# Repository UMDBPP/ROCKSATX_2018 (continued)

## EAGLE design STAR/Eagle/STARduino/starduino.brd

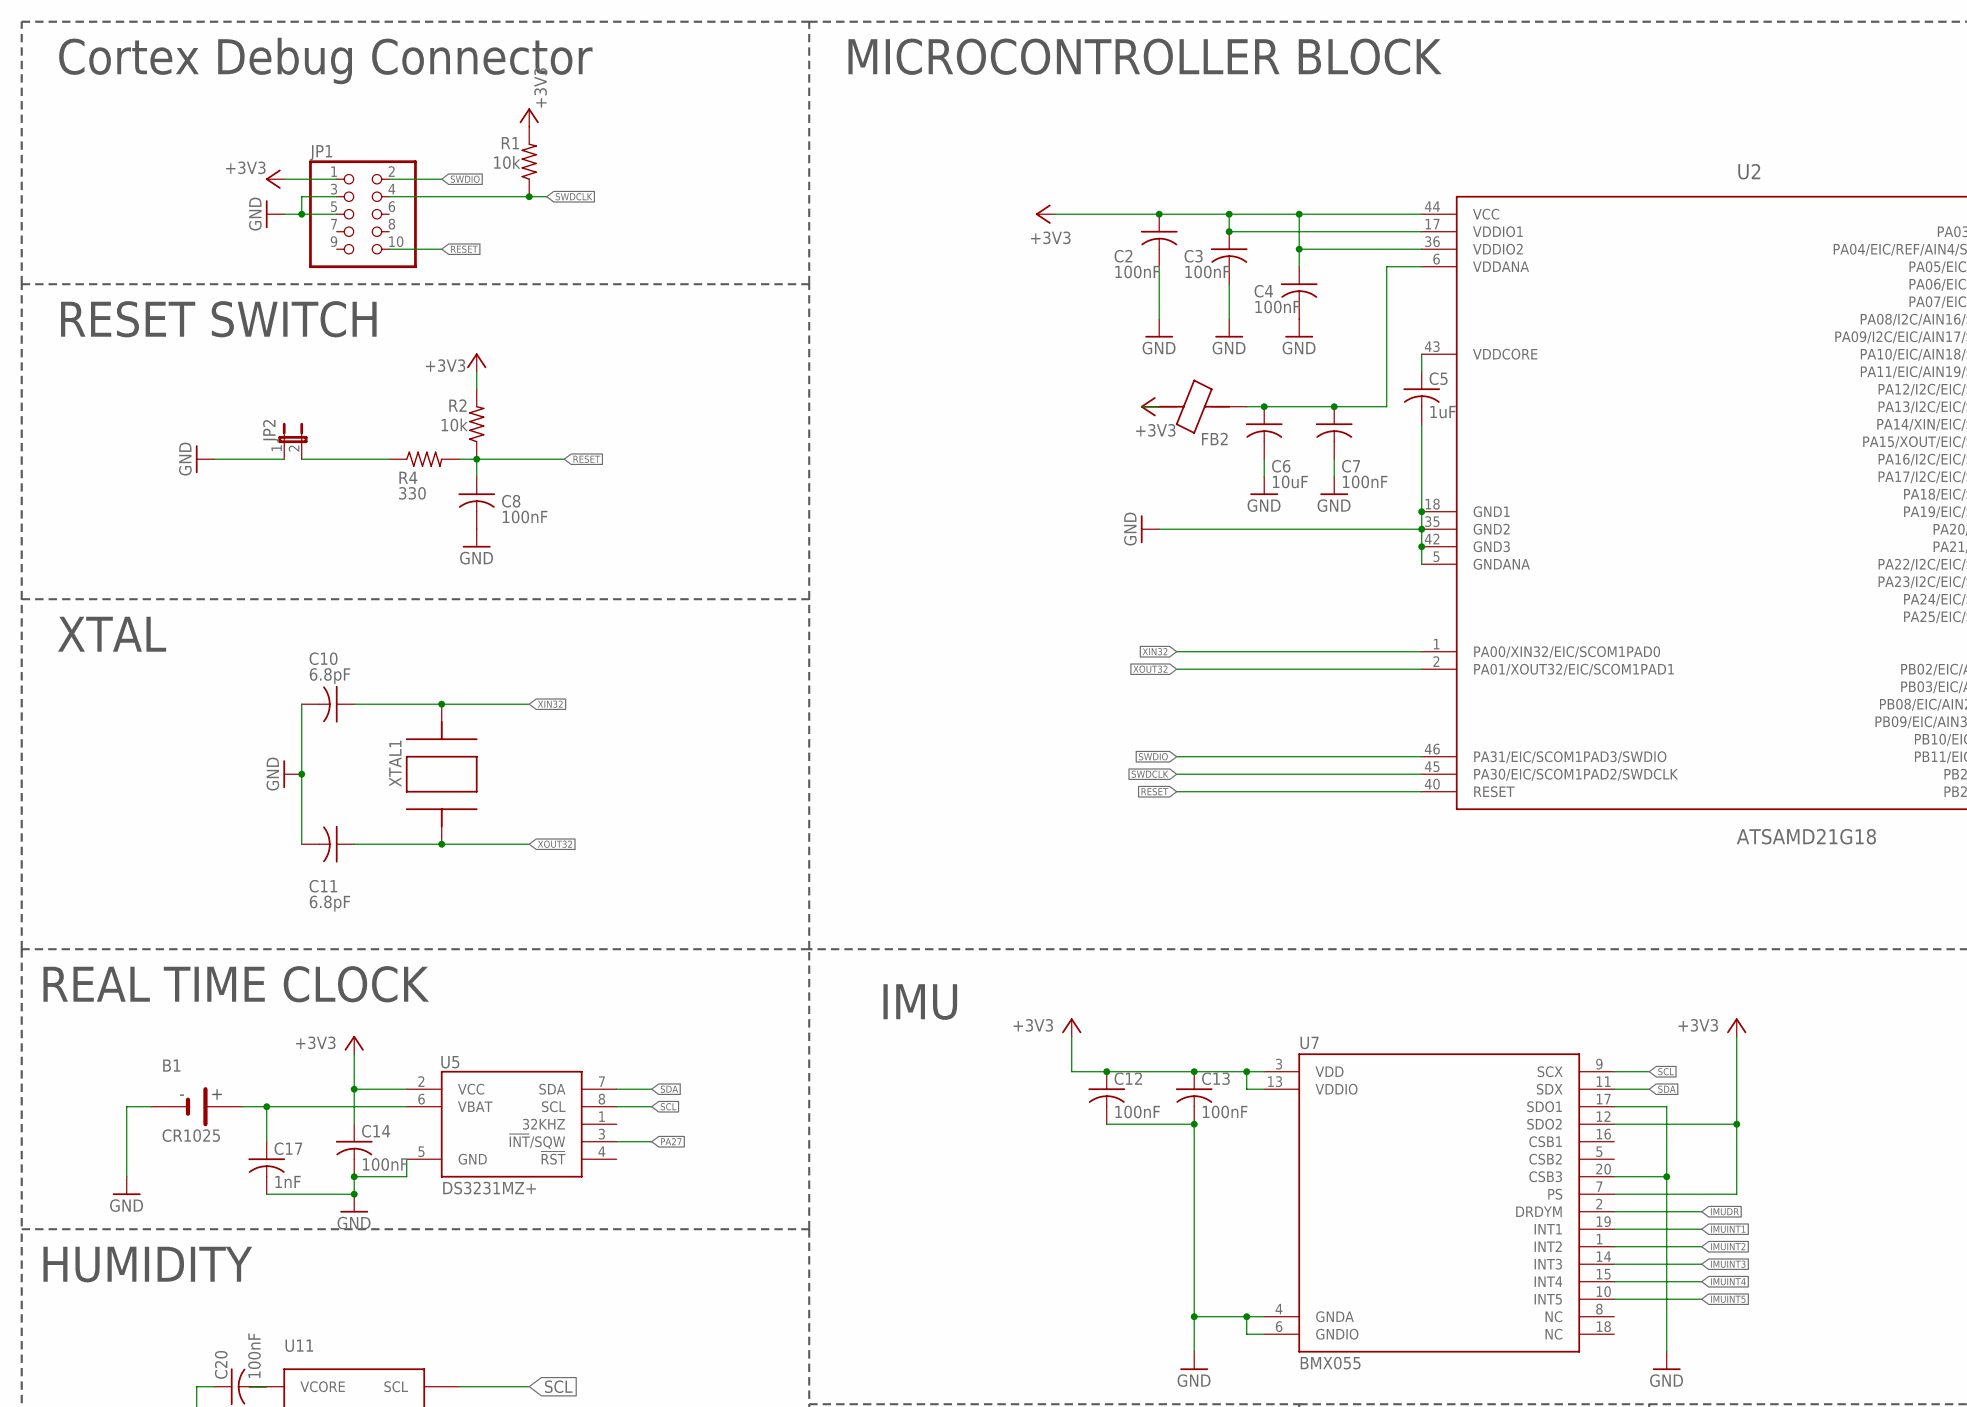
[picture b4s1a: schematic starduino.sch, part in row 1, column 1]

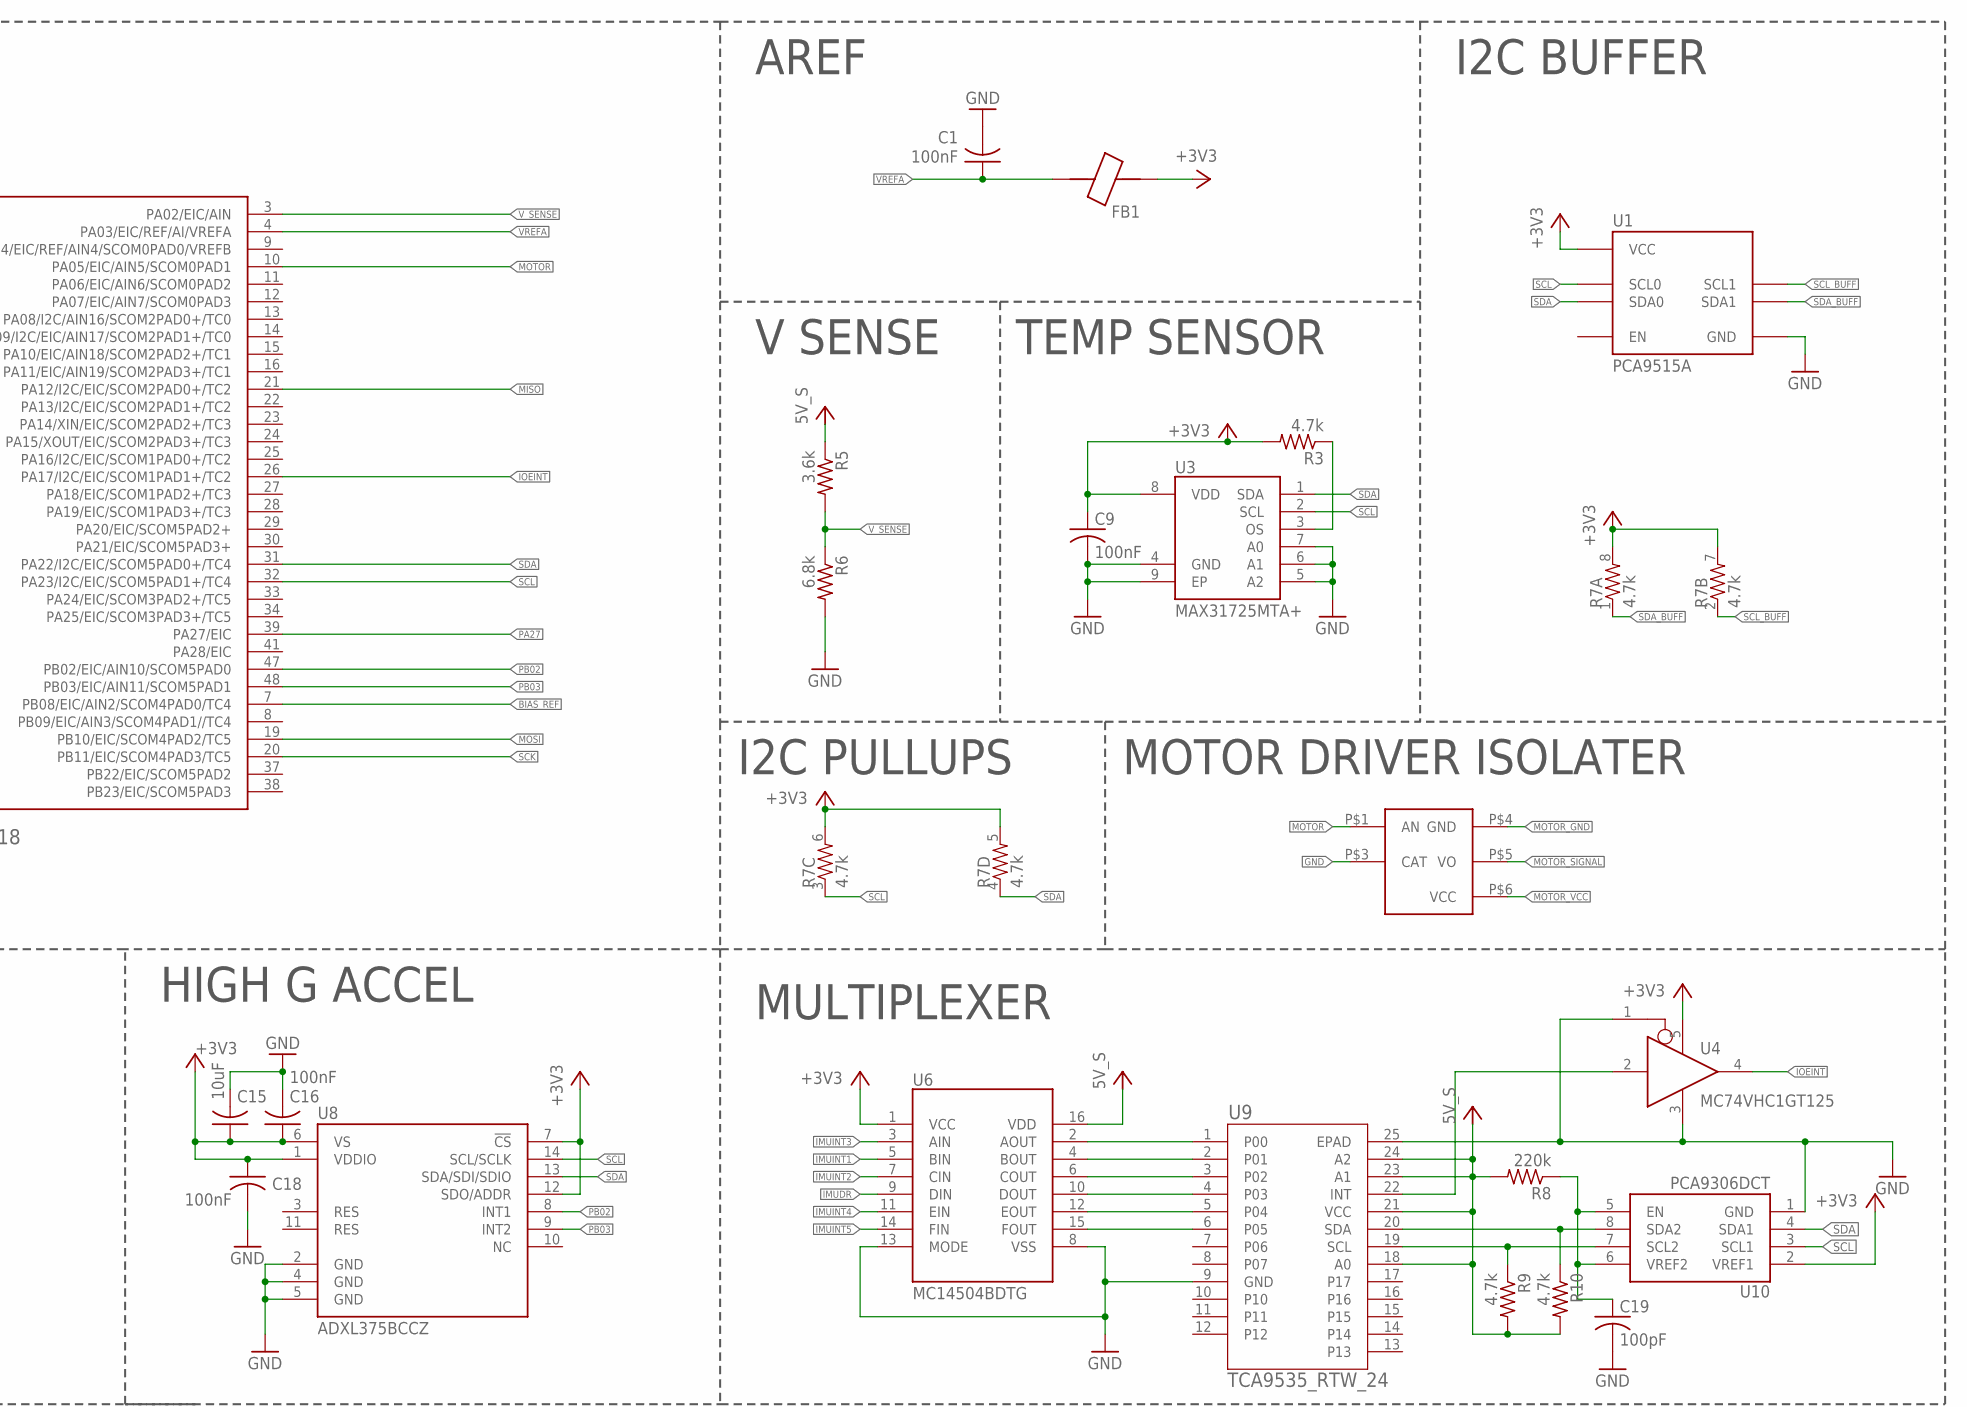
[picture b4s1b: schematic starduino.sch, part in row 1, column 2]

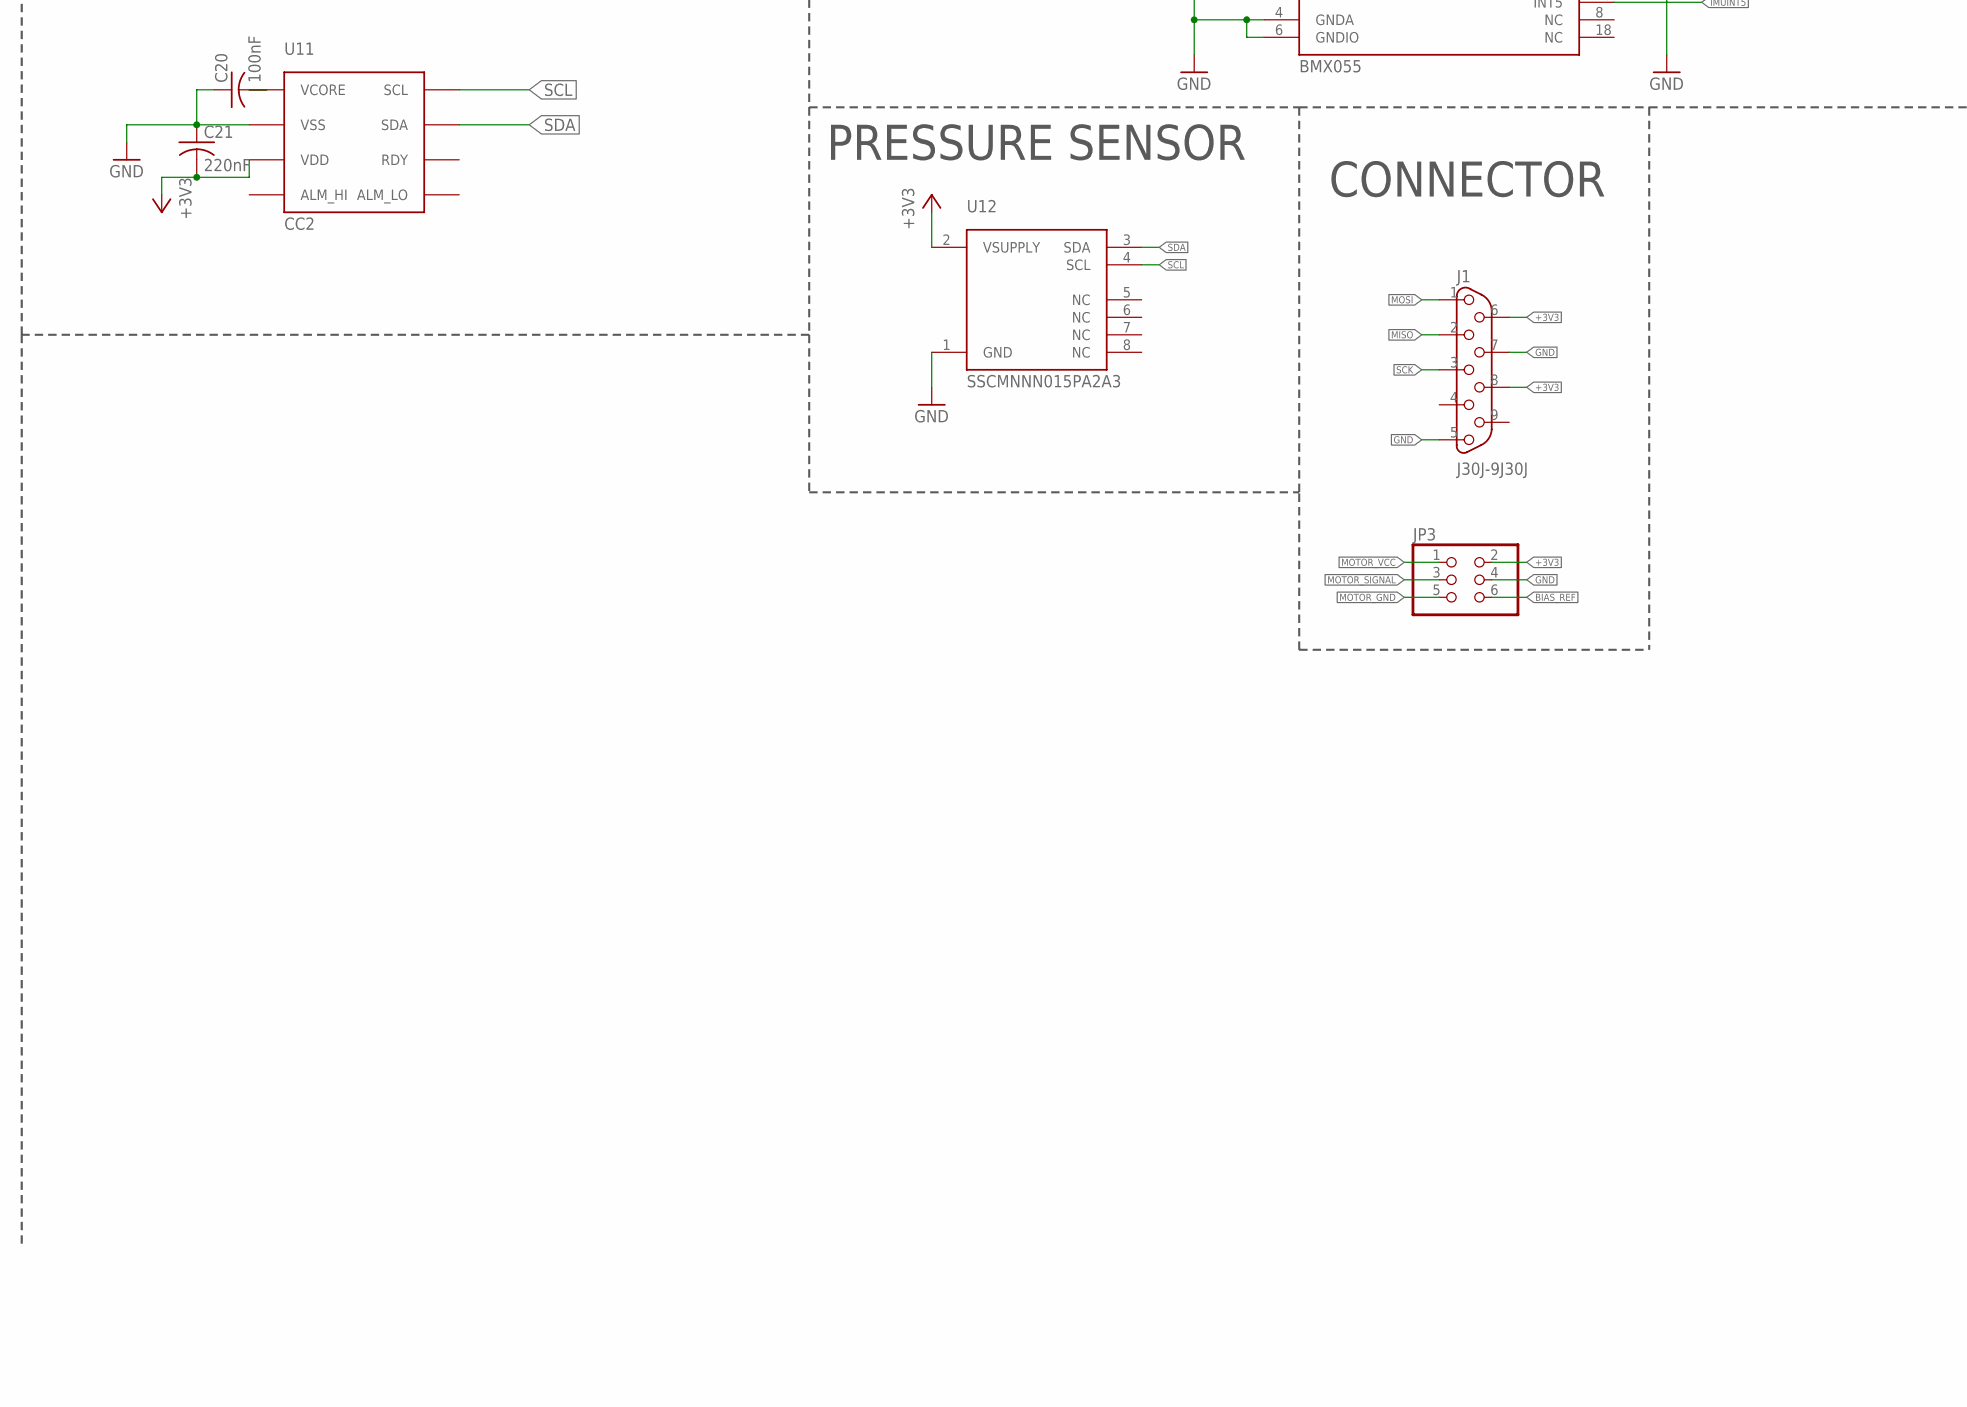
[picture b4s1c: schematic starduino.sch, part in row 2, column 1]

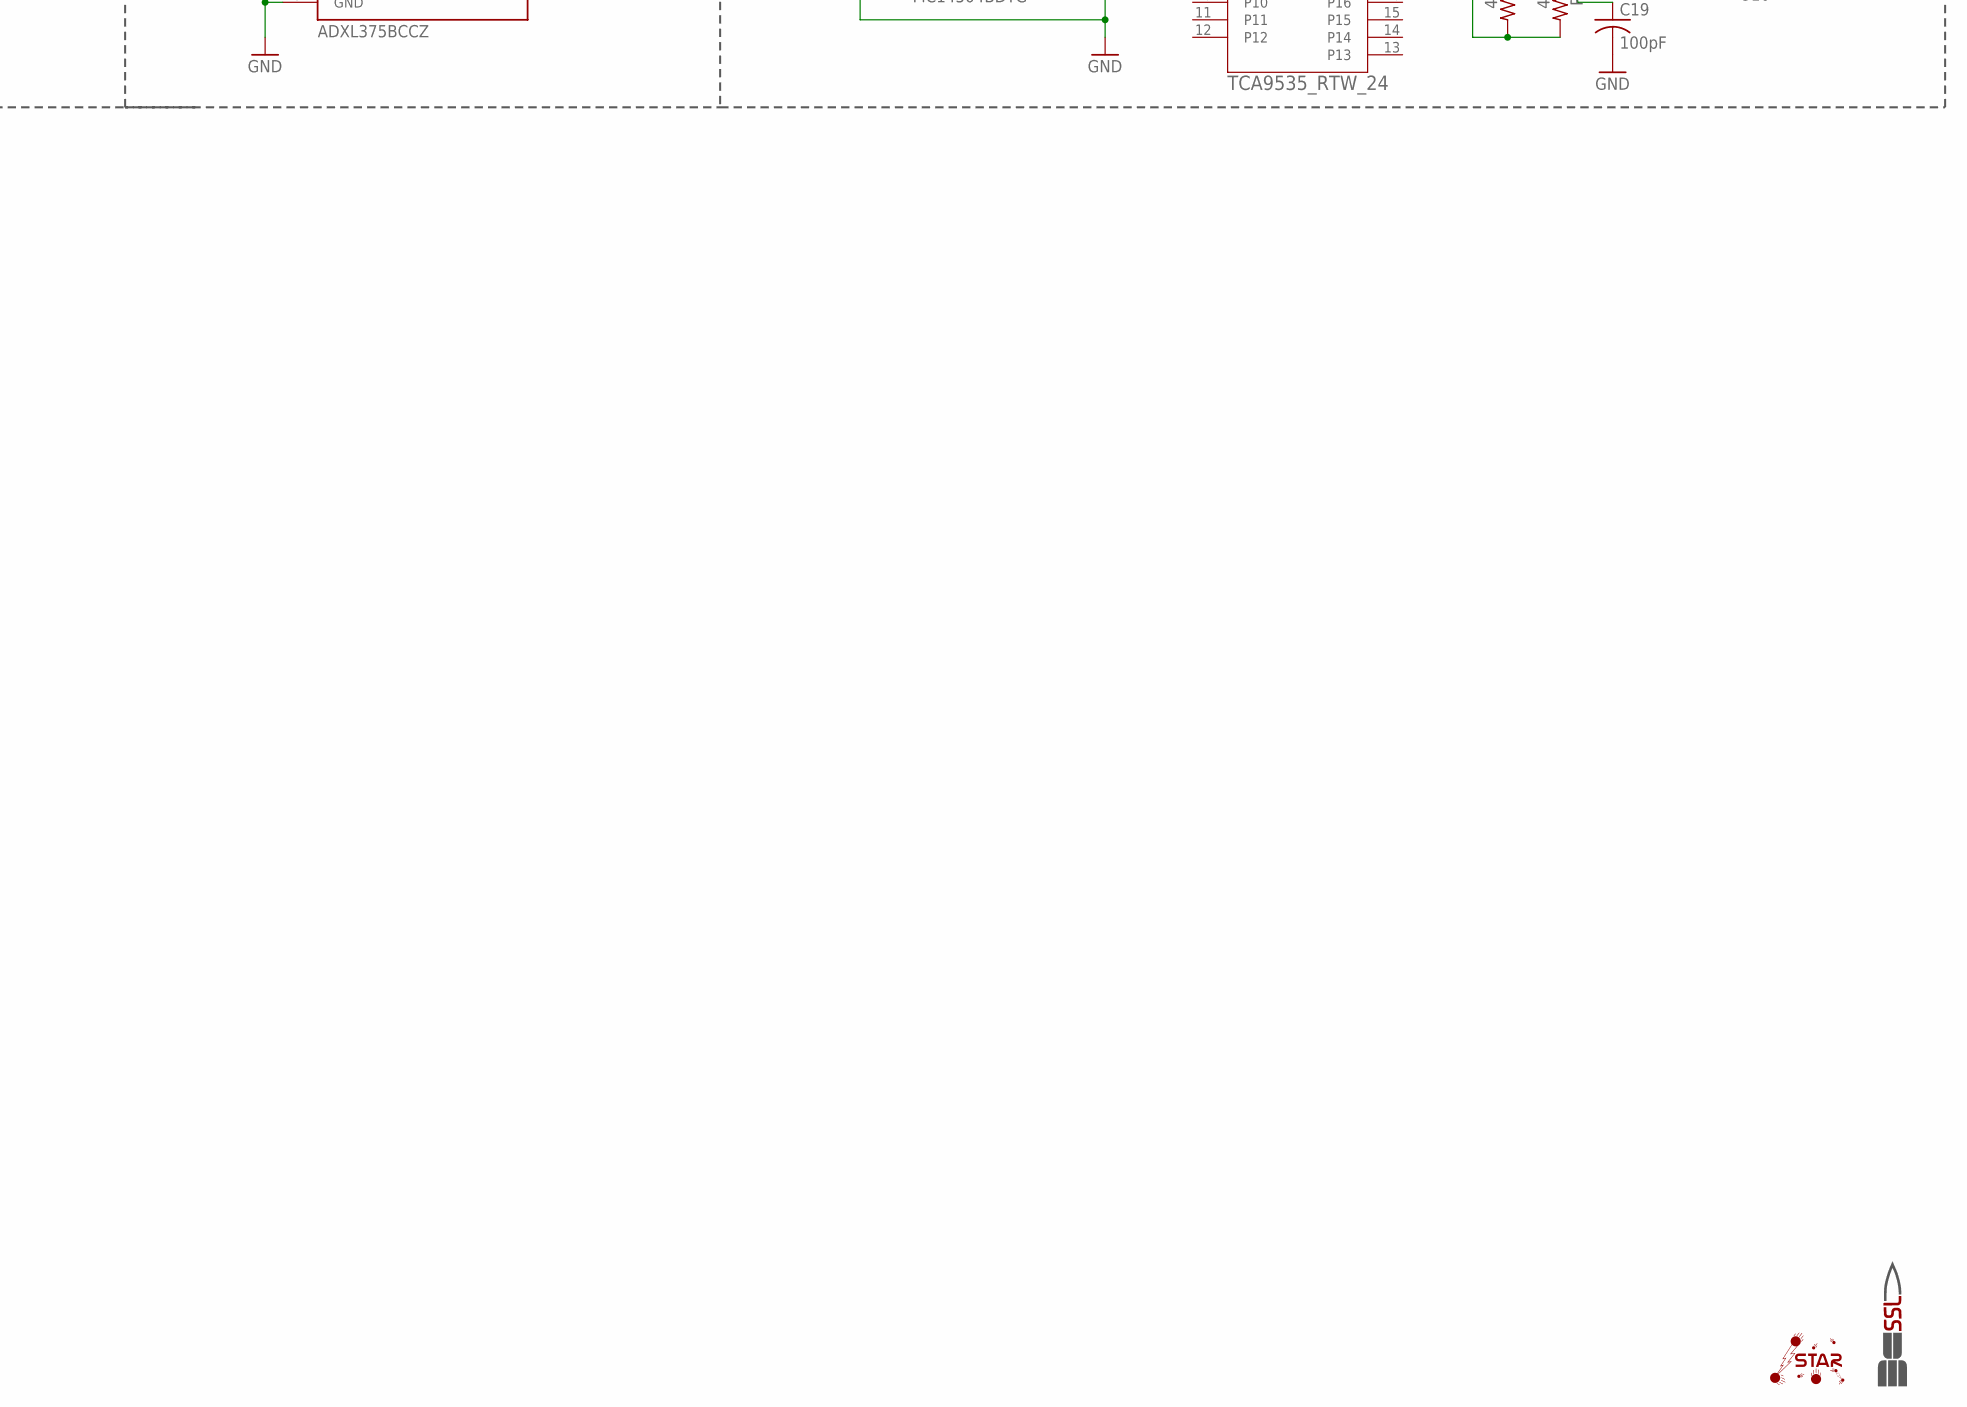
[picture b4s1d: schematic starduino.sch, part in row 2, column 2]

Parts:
B1: CR1025
C1, C2, C3, C4, C7, C8, C9, C12, C13, C14, C16, C18, C20: 100nF; C0603
C5: 1uF; C0603
C6, C15: 10uF; C0603
C10, C11: 6.8pF; C0603
C17: 1nF; C0603
C19: 100pF; C0603
C21: 220nF; C0603
FB1, FB2: BLM18KG221BH1D; 0603
IMAG1: SSL.3IN_SILK; SSL_SILK_.3IN
IMAG2: STAR; STAR_.3IN
J1: J30J-9J30J; ZKN-9
JP1: PINHD-2X5; 2X05
JP2: JUMPER-2PTH; 1X02
JP3: PINHD-2X3; 2X03
R1, R2: 10k; R0603
R3, R9, R10: 4.7k; R0603
R4: 330; R0603
R5: 3.6k; R0603
R6: 6.8k; R0603
R7: 4.7k; 0603-ARV
R8: 220k; R0603
U1: PCA9515A; TSSOP8
U2: ATSAMD21G18; 48-TQFP
U3: MAX31725MTA+; DFN-8
U4: MC74VHC1GT125; SC-70-5
U5: DS3231MZ+; SOIC-8
U6: MC14504BDTG; TSSOP16
U7: BMX055; LGA-20
U8: ADXL375BCCZ; LGA-14
U9: TCA9535_RTW_24; RTW24_2P45X2P45
U10: PCA9306DCT; SSOP8
U11: CC2
U12: SSCMNNN015PA2A3; HSC-SMT-8
U$1: FODM8061-D; SO5
XTAL1: ABS07AIG-32.768KHZ-1-T; 2-SMD

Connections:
5V_S: R5.1, R8.2, R9.2, R10.2, U6.16 (VDD), U9.18 (A0), U9.21 (VCC), U9.23 (A1), U9.24 (A2)
+3V3: C2.1, C3.1, C4.1, C9.1, C12.1, C13.1, C14.1, C15.1, C16.1, C18.1, C21.2, FB1.2, FB2.1, J1.6, J1.8, JP1.1, JP3.2, R1.2, R2.2, R3.2, R7.5 (2), R7.6 (2), R7.7 (2), R7.8 (2), U1.P$8 (VCC), U2.17 (VDDIO1), U2.36 (VDDIO2), U2.44 (VCC), U3.8 (VDD), U4.5 (VIN), U5.2 (VCC), U6.1 (VCC), U7.3 (VDD), U7.7 (PS), U7.12 (SDO2), U7.13 (VDDIO), U8.1 (VDDIO), U8.6 (VS), U8.7 (!CS!), U8.12 (SDO/ADDR), U10.2 (VREF1), U11.P$7 (VDD), U12.2 (VSUPPLY)
BIAS_REF: JP3.6, U2.7 (PB08/EIC/AIN2/SCOM4PAD0/TC4)
GND: B1.3 (-), C1.2, C2.2, C3.2, C4.2, C5.2, C6.2, C7.2, C8.2, C9.2, C10.2, C11.2, C12.2, C13.2, C14.2, C15.2, C16.2, C17.2, C18.2, C19.2, C20.1, C21.1, J1.5, J1.7, JP1.3, JP1.5, JP2.1, JP3.4, R6.2, U1.P$4 (GND), U2.5 (GNDANA), U2.18 (GND1), U2.35 (GND2), U2.42 (GND3), U3.4 (GND), U3.5 (A2), U3.6 (A1), U3.7 (A0), U3.9 (EP), U4.1 (OE), U4.3 (GND), U5.5 (GND), U6.8 (VSS), U6.13 (MODE), U7.4 (GNDA), U7.6 (GNDIO), U7.17 (SDO1), U7.20 (CSB3), U8.2 (GND), U8.4 (GND), U8.5 (GND), U9.9 (GND), U9.25 (EPAD), U10.1 (GND), U11.P$6 (VSS), U12.1 (GND), U$1.P$3 (CAT)
IMUDR: U6.9 (DIN), U7.2 (DRDYM)
IMUINT1: U6.5 (BIN), U7.19 (INT1)
IMUINT2: U6.7 (CIN), U7.1 (INT2)
IMUINT3: U6.3 (AIN), U7.14 (INT3)
IMUINT4: U6.11 (EIN), U7.15 (INT4)
IMUINT5: U6.14 (FIN), U7.10 (INT5)
IOEINT: U2.26 (PA17/I2C/EIC/SCOM1PAD1+/TC2), U4.4 (Y)
MISO: J1.2, U2.21 (PA12/I2C/EIC/SCOM2PAD0+/TC2)
MOSI: J1.1, U2.19 (PB10/EIC/SCOM4PAD2/TC5)
MOTOR: U2.10 (PA05/EIC/AIN5/SCOM0PAD1), U$1.P$1 (AN)
MOTOR_GND: JP3.5, U$1.P$4 (GND)
MOTOR_SIGNAL: JP3.3, U$1.P$5 (VO)
MOTOR_VCC: JP3.1, U$1.P$6 (VCC)
unnamed: C20.2, U11.P$5 (VCORE)
unnamed: C5.1, U2.43 (VDDCORE)
unnamed: R3.1, U3.3 (OS)
unnamed: JP2.2, R4.1
unnamed: B1.1 (+), B1.2 (+), C17.1, U5.6 (VBAT)
unnamed: C6.1, C7.1, FB2.2, U2.6 (VDDANA)
unnamed: U6.2 (AOUT), U9.1 (P00)
unnamed: U6.4 (BOUT), U9.2 (P01)
unnamed: U4.2 (A), U9.22 (INT)
unnamed: U6.6 (COUT), U9.3 (P02)
unnamed: U6.10 (DOUT), U9.4 (P03)
unnamed: U6.12 (EOUT), U9.5 (P04)
unnamed: U6.15 (FOUT), U9.6 (P05)
unnamed: R10.1, U9.20 (SDA), U10.8 (SDA2)
unnamed: R9.1, U9.19 (SCL), U10.7 (SCL2)
unnamed: C19.1, R8.1, U10.5 (EN), U10.6 (VREF2)
PA27: U2.39 (PA27/EIC), U5.3 (!INT!/SQW)
PB02: U2.47 (PB02/EIC/AIN10/SCOM5PAD0), U8.8 (INT1)
PB03: U2.48 (PB03/EIC/AIN11/SCOM5PAD1), U8.9 (INT2)
RESET: C8.1, JP1.10, R2.1, R4.2, U2.40 (RESET)
SCK: J1.3, U2.20 (PB11/EIC/SCOM4PAD3/TC5)
SCL: R7.3 (1), U1.P$2 (SCL0), U2.32 (PA23/I2C/EIC/SCOM5PAD1+/TC4), U3.2 (SCL), U5.8 (SCL), U7.9 (SCX), U8.14 (SCL/SCLK), U10.3 (SCL1), U11.P$4 (SCL), U12.4 (SCL)
SCL_BUFF: R7.2 (1), U1.P$7 (SCL1)
SDA: R7.4 (1), U1.P$3 (SDA0), U2.31 (PA22/I2C/EIC/SCOM5PAD0+/TC4), U3.1 (SDA), U5.7 (SDA), U7.11 (SDX), U8.13 (SDA/SDI/SDIO), U10.4 (SDA1), U11.P$3 (SDA), U12.3 (SDA)
SDA_BUFF: R7.1, U1.P$6 (SDA1)
SWDCLK: JP1.4, R1.1, U2.45 (PA30/EIC/SCOM1PAD2/SWDCLK)
SWDIO: JP1.2, U2.46 (PA31/EIC/SCOM1PAD3/SWDIO)
VREFA: C1.1, FB1.1, U2.4 (PA03/EIC/REF/AI/VREFA)
V_SENSE: R5.2, R6.1, U2.3 (PA02/EIC/AIN)
XIN32: C10.1, U2.1 (PA00/XIN32/EIC/SCOM1PAD0), XTAL1.P2 (2)
XOUT32: C11.1, U2.2 (PA01/XOUT32/EIC/SCOM1PAD1), XTAL1.P1 (1)

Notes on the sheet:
MICROCONTROLLER BLOCK
Cortex Debug Connector
RESET SWITCH
XTAL
AREF
V SENSE
I2C PULLUPS
HIGH G ACCEL
TEMP SENSOR
REAL TIME CLOCK
IMU
HUMIDITY
MULTIPLEXER
I2C BUFFER
PRESSURE SENSOR
CONNECTOR
MOTOR DRIVER ISOLATER

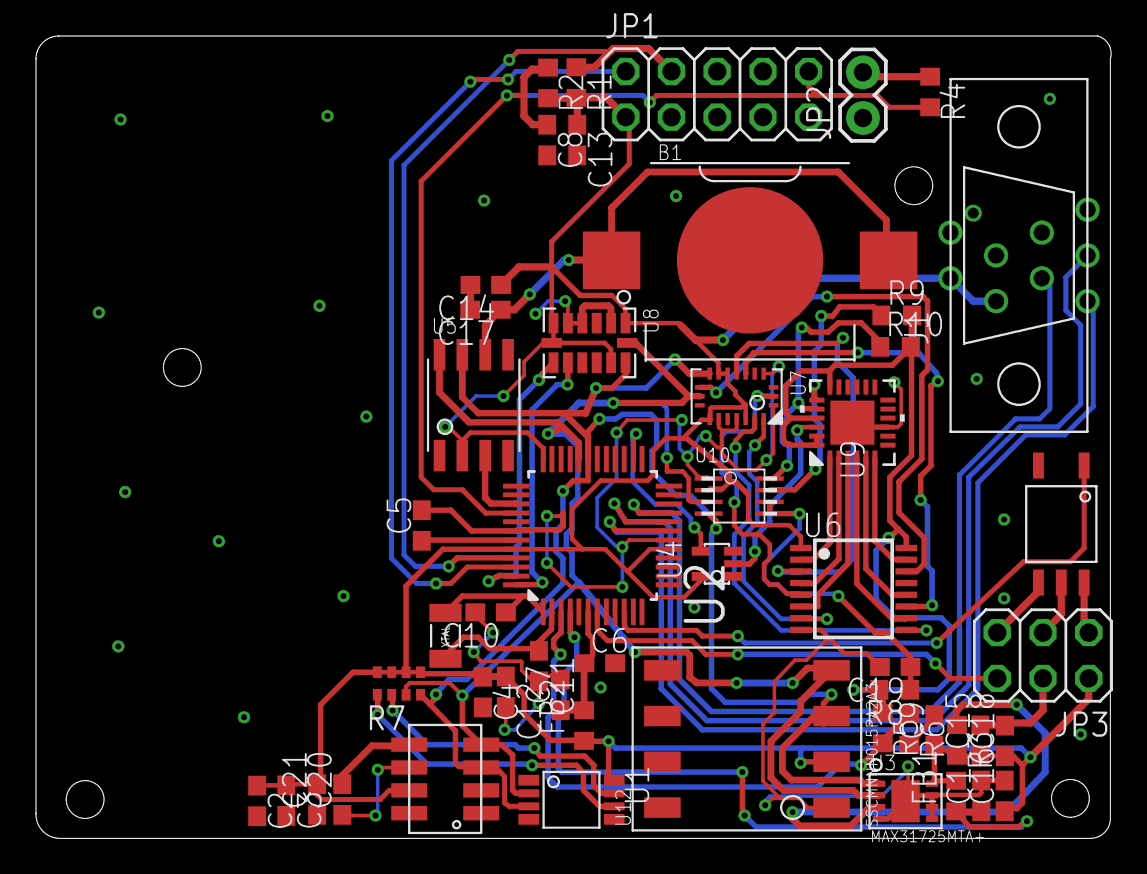
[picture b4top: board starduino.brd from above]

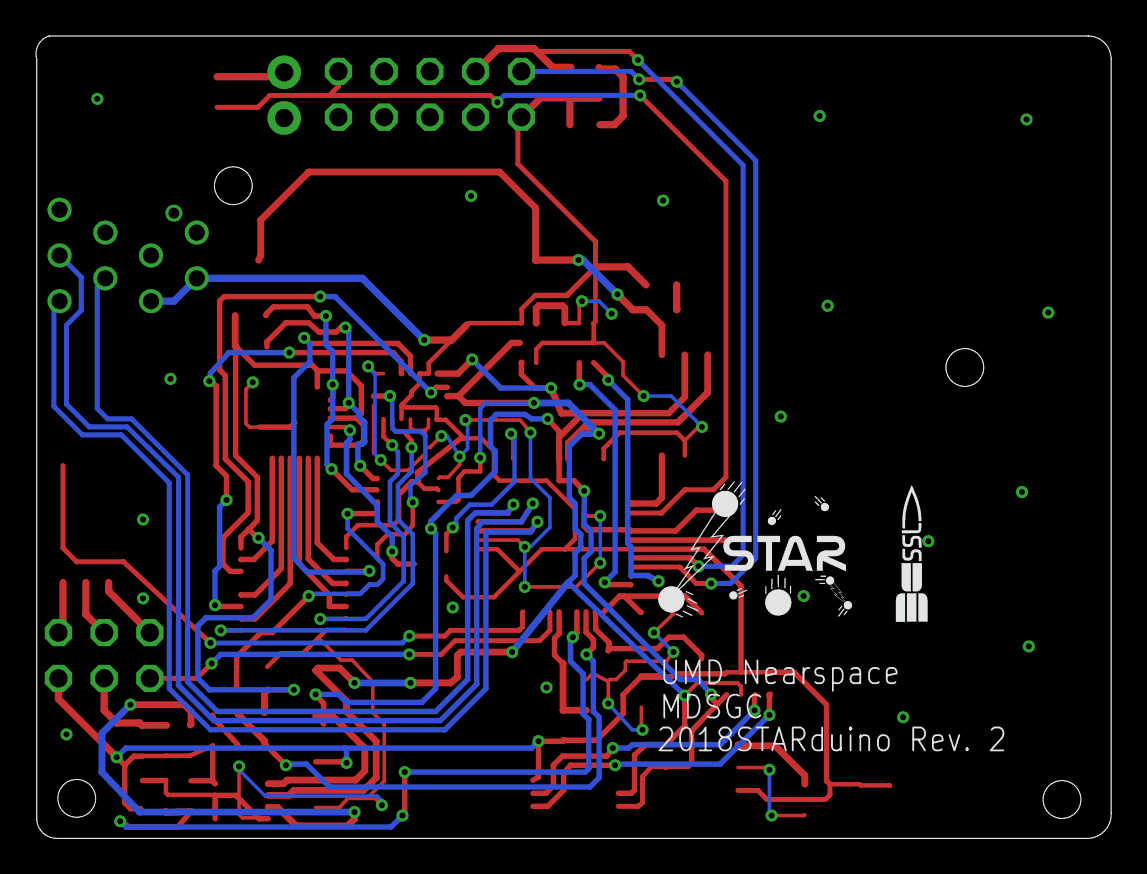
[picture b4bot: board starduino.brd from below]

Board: 2 copper layers, 59.7 x 44.6 mm, 54 parts (2 on the bottom side), 48 nets.

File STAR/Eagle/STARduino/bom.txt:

Partlist exported from C:/UMD/BPP/ROCKSAT X/2018/ROCKSATX_2018/STAR/Eagle/STARduino/starduino.sch at 7/8/2018 9:45

Qty Value                   Device                 Package         Parts                                                    Description                MANUFACTURER_PART_NUMBER VENDOR           
1                           JUMPER-2PTH            1X02            JP2                                                      Jumper                                                               
1                           PINHD-2X3              2X03            JP3                                                      PIN HEADER                                                           
1                           PINHD-2X5              2X05            JP1                                                      PIN HEADER                                                           
13  100nF                   C-USC0603              C0603           C1, C2, C3, C4, C7, C8, C9, C12, C13, C14, C16, C18, C20 CAPACITOR, American symbol                                           
1   100pF                   C-USC0603              C0603           C19                                                      CAPACITOR, American symbol                                           
2   10k                     R-US_R0603             R0603           R1, R2                                                   RESISTOR, American symbol                                            
2   10uF                    C-USC0603              C0603           C6, C15                                                  CAPACITOR, American symbol                                           
1   1nF                     C-USC0603              C0603           C17                                                      CAPACITOR, American symbol                                           
1   1uF                     C-USC0603              C0603           C5                                                       CAPACITOR, American symbol                                           
1   220k                    R-US_R0603             R0603           R8                                                       RESISTOR, American symbol                                            
1   220nF                   C-USC0603              C0603           C21                                                      CAPACITOR, American symbol                                           
1   3.6k                    R-US_R0603             R0603           R5                                                       RESISTOR, American symbol                                            
1   330                     R-US_R0603             R0603           R4                                                       RESISTOR, American symbol                                            
3   4.7k                    R-US_R0603             R0603           R3, R9, R10                                              RESISTOR, American symbol                                            
1   4.7k                    RESISTOR-ARRAY0603-ARV 0603-ARV        R7                                                       Array Chip Resistor                                                  
1   6.8k                    R-US_R0603             R0603           R6                                                       RESISTOR, American symbol                                            
2   6.8pF                   C-USC0603              C0603           C10, C11                                                 CAPACITOR, American symbol                                           
1   ABS07AIG-32.768KHZ-1-T  ABS07AIG-32.768KHZ-1-T 2-SMD           XTAL1                                                                                                                         
1   ADXL375BCCZ             ADXL375BCCZ            LGA-14          U8                                                                                                                            
1   ATSAMD21G18             ATSAMD21G18            48-TQFP         U2                                                                                                                            
2   BLM18KG221BH1D          FERRITE_BEAD-0603      0603            FB1, FB2                                                                                                                      
1   BMX055                  BMX055                 LGA-20          U7                                                                                                                            
1   CC2                     CC2                    CC2             U11                                                                                                                           
1   CR1025                  CR1025                 CR1025          B1                                                                                                                            
1   DS3231MZ+               DS3231MZ+              SOIC-8          U5                                                                                                                            
1   FODM8061-D              FODM8061-D             SO5             U$1                                                                                                                           
1   J30J-9J30J              J30J-9J30J             ZKN-9           J1                                                                                                                            
1   MAX31725MTA+            MAX31725MTA+           DFN-8           U3                                                                                                                            
1   MC14504BDTG             MC14504BDTG            TSSOP16         U6                                                                                                                            
1   MC74VHC1GT125           MC74VHC1GT125          SC-70-5         U4                                                                                                                            
1   PCA9306DCT              PCA9306DCT             SSOP8           U10                                                                                                                           
1   PCA9515A                PCA9515A               TSSOP8          U1                                                                                                                            
1   SSCMNNN015PA2A3         SSCMNNN015PA2A3        HSC-SMT-8       U12                                                                                                                           
1   SSL.3IN_SILK            SSL.3IN_SILK           SSL_SILK_.3IN   IMAG1                                                                                                                         
1   STAR                    STAR                   STAR_.3IN       IMAG2                                                                                                                         
1   TCA9535_RTW_24          TCA9535_RTW_24         RTW24_2P45X2P45 U9                                                                                  tca9535_rtw_24           Texas Instruments

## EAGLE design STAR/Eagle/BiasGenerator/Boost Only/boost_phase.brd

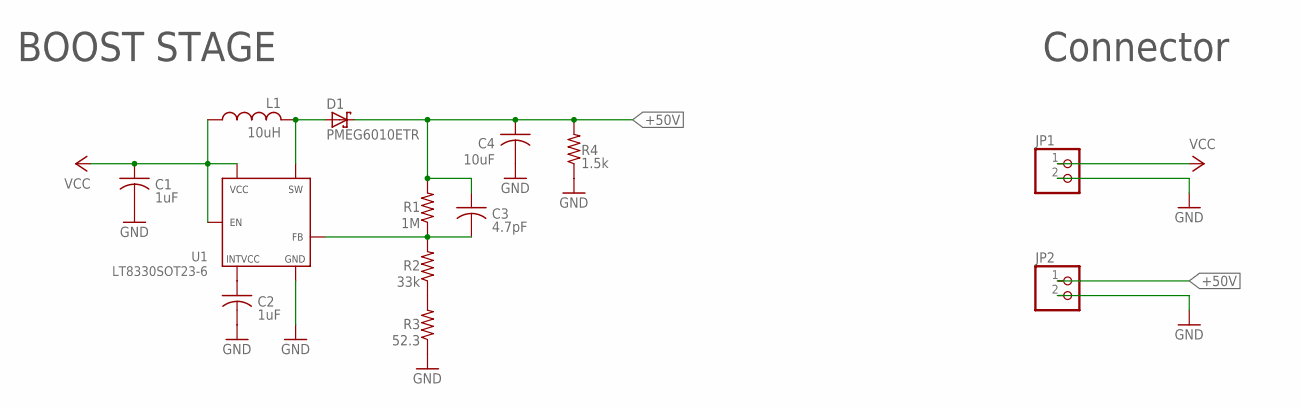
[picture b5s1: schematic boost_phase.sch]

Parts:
C1, C2: 1uF; C0805
C3: 4.7pF; C0805
C4: 10uF; 2J-LEAD
D1: PMEG6010ETR; SOD123
JP1, JP2: SCREWTERM_1X2
L1: 10uH; PQ2614
R1: 1M; R0805
R2: 33k; R0805
R3: 52.3; R0805
R4: 1.5k; R2512
U1: LT8330SOT23-6; SOT23-6

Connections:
+50V: C3.1, C4.P$1 (1), D1.P$2 (C), JP2.1, R1.2, R4.2
GND: C1.2, C2.2, C4.P$2 (2), JP1.2, JP2.2, R3.1, R4.1, U1.2 (GND)
unnamed: C2.1, U1.5 (INTVCC)
unnamed: R2.1, R3.2
unnamed: D1.P$1 (A), L1.P$3 (2), U1.1 (SW)
unnamed: C3.2, R1.1, R2.2, U1.3 (FB)
VCC: C1.1, JP1.1, L1.P$2 (1), U1.4 (EN), U1.6 (VCC)

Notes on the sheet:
BOOST STAGE
Connector

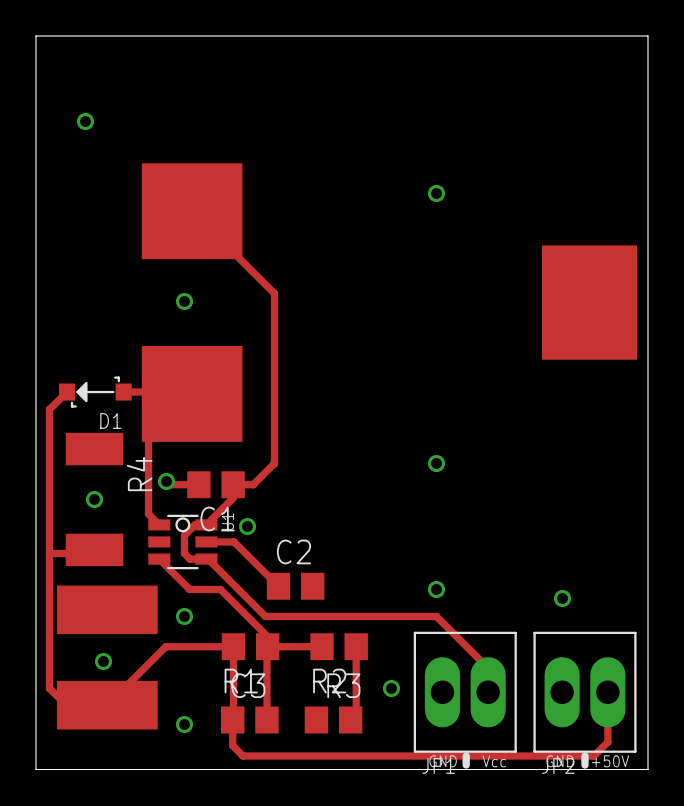
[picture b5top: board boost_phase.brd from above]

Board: 2 copper layers, 34.0 x 40.8 mm, 13 parts (0 on the bottom side), 7 nets.
